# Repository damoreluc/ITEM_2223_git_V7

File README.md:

# Hardware progetto ITEM
## ISIS Bassa Friulana Cervignano del Friuli - ISIS Malignani Udine - Danieli 

Progetto hardware delle schede del sistema di acquisizione dati del _Banco di prova per riduttori meccanici_<br>
Il progetto è realizzato con il cad Eagle.

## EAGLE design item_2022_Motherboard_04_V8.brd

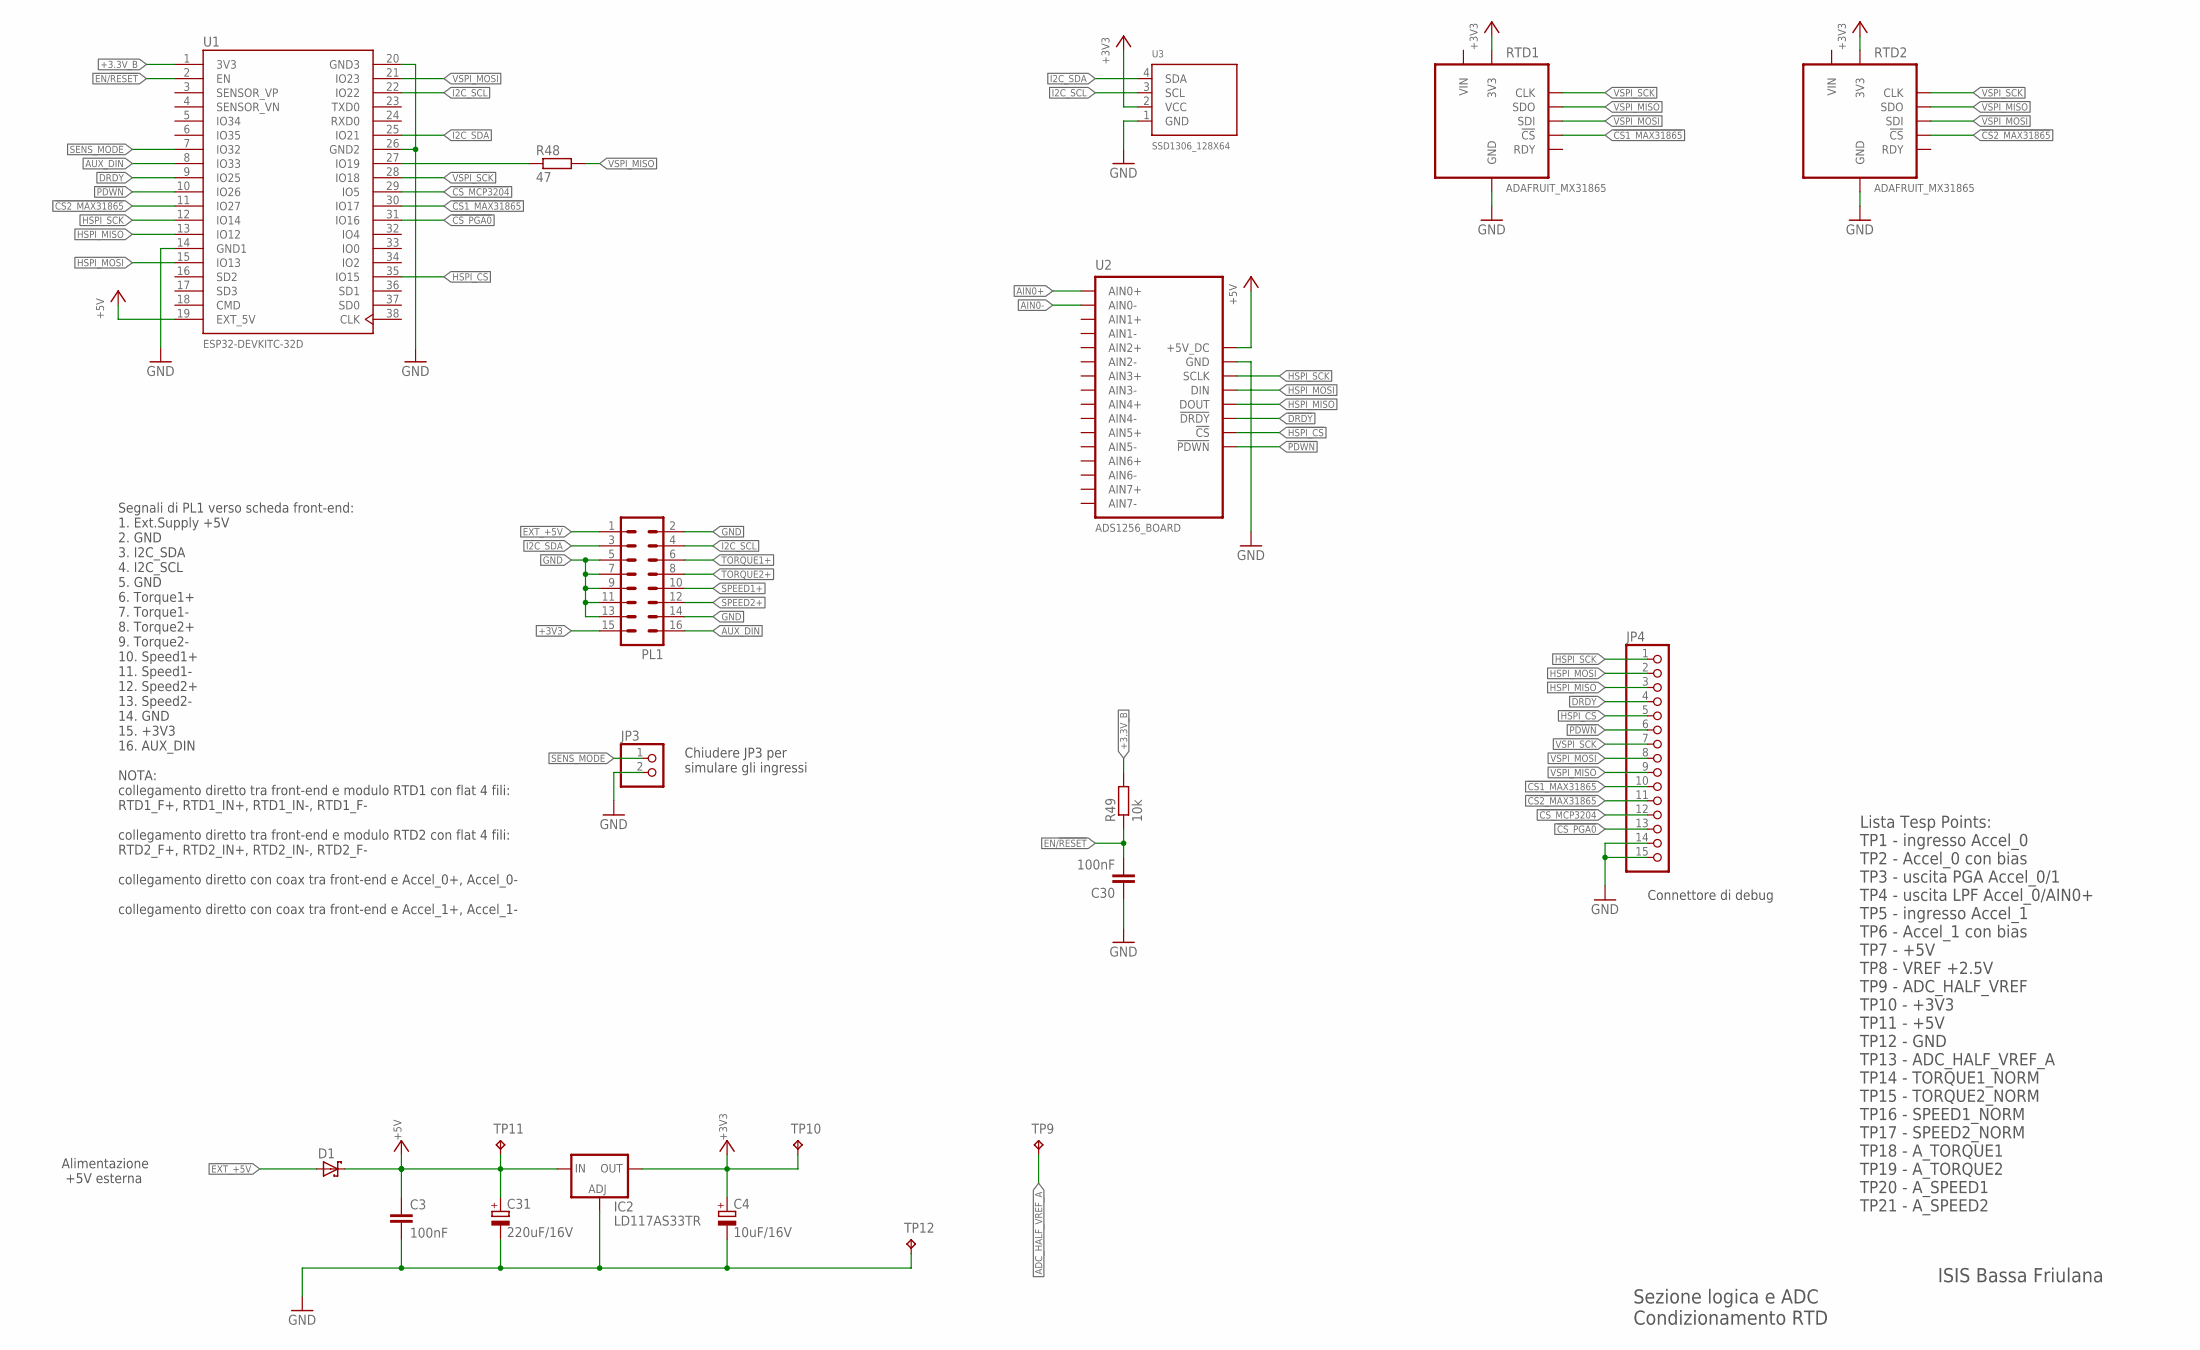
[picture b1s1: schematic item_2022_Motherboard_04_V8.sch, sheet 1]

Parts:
C3: 100nF; C0805K
C4: 10uF/16V; E2,5-6
C30: 100nF; C0805
C31: 220uF/16V; E3,5-10
D1: SCHOTTKY-DIODEDO35-7; DO35-7
IC2: LD117AS33TR; SOT223
JP3: PINHD-1X2; 1X02
JP4: PINHD-1X15; 1X15
PL1: 16H
R48: 47; R0805
R49: 10k; R0805
RTD1, RTD2: ADAFRUIT_MX31865; ADAFRUIT_MAX31865
TP9, TP10, TP11: TPTP16SQ; TP16SQ
TP12: TPTP14R; TP14R
U1: ESP32-DEVKITC-32D; MODULE_ESP32-DEVKITC-32D
U2: ADS1256_BOARD
U3: SSD1306_128X64; 128X64

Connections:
!CS1_MAX31865!: JP4.10, RTD1.P7 (!CS!), U1.30 (IO17)
!CS2_MAX31865!: JP4.11, RTD2.P7 (!CS!), U1.11 (IO27)
!CS_MCP3204!: JP4.12, U1.29 (IO5); also elsewhere on the board
!CS_PGA0!: JP4.13, U1.31 (IO16); also elsewhere on the board
!DRDY!: JP4.4, U1.9 (IO25), U2.!DRDY!
!HSPI_CS!: JP4.5, U1.35 (IO15), U2.!CS!
!PDWN!: JP4.6, U1.10 (IO26), U2.PDWN (!PDWN!)
+3.3V_B: R49.2, U1.1 (3V3)
+3V3: C4.+, IC2.4 (OUT), PL1.15, RTD1.P3 (3V3), RTD2.P3 (3V3), TP10.TP, U3.2 (VCC); also elsewhere on the board
+5V: C3.1, C31.+, D1.C, IC2.3 (IN), TP11.TP, U1.19 (EXT_5V), U2.5V_DC (+5V_DC); also elsewhere on the board
ADC_HALF_VREF_A: TP9.TP; also elsewhere on the board
AIN0+: U2.AIN0+; also elsewhere on the board
AIN0-: U2.AIN0-; also elsewhere on the board
AUX_DIN: PL1.16, U1.8 (IO33)
EN/!RESET!: C30.2, R49.1, U1.2 (EN)
EXT_+5V: D1.A, PL1.1
GND: C3.2, C4.-, C30.1, C31.-, IC2.1 (ADJ), JP3.2, JP4.14, JP4.15, PL1.2, PL1.5, PL1.7, PL1.9, PL1.11, PL1.13, PL1.14, RTD1.P2 (GND), RTD2.P2 (GND), TP12.TP, U1.14 (GND1), U1.20 (GND3), U1.26 (GND2), U2.GND, U3.1 (GND); also elsewhere on the board
HSPI_MISO: JP4.3, U1.13 (IO12), U2.DOUT
HSPI_MOSI: JP4.2, U1.15 (IO13), U2.DIN
HSPI_SCK: JP4.1, U1.12 (IO14), U2.SCLK
I2C_SCL: PL1.4, U1.22 (IO22), U3.3 (SCL)
I2C_SDA: PL1.3, U1.25 (IO21), U3.4 (SDA)
unnamed: R48.1, U1.27 (IO19)
SENS_MODE: JP3.1, U1.7 (IO32)
SPEED1+: PL1.10; also elsewhere on the board
SPEED2+: PL1.12; also elsewhere on the board
TORQUE1+: PL1.6; also elsewhere on the board
TORQUE2+: PL1.8; also elsewhere on the board
VIN: RTD1.P1 (VIN), RTD2.P1 (VIN)
VSPI_MISO: JP4.9, R48.2, RTD1.P5 (SDO), RTD2.P5 (SDO); also elsewhere on the board
VSPI_MOSI: JP4.8, RTD1.P6 (SDI), RTD2.P6 (SDI), U1.21 (IO23); also elsewhere on the board
VSPI_SCK: JP4.7, RTD1.P4 (CLK), RTD2.P4 (CLK), U1.28 (IO18); also elsewhere on the board

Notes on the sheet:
Sezione logica e ADC Condizionamento RTD
ISIS Bassa Friulana
Lista Tesp Points: TP1 - ingresso Accel_0 TP2 - Accel_0 con bias TP3 - uscita PGA Accel_0/1 TP4 - uscita LPF Accel_0/AIN0+ TP5 - ingresso Accel_1 TP6 - Accel_1 con bias TP7 - +5V TP8 - VREF +2.5V TP9 - ADC_HALF_VREF TP10 - +3V3 TP11 - +5V TP12 - GND TP13 - ADC_HALF_VREF_A TP14 - TORQUE1_NORM TP15 -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
Segnali di PL1 verso scheda front-end: 1. Ext.Supply +5V 2. GND 3. I2C_SDA 4. I2C_SCL 5. GND 6. Torque1+ 7. Torque1- 8. Torque2+ 9. Torque2- 10. Speed1+ 11. Speed1- 12. Speed2+ 13. Speed2- 14. GND 15. +3V3 16. AUX_DIN NOTA: collegamento diretto tra front-end e modulo RTD1 con flat 4 fili: RTD1_F+, 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
Alimentazione +5V esterna
Chiudere JP3 per simulare gli ingressi
Connettore di debug

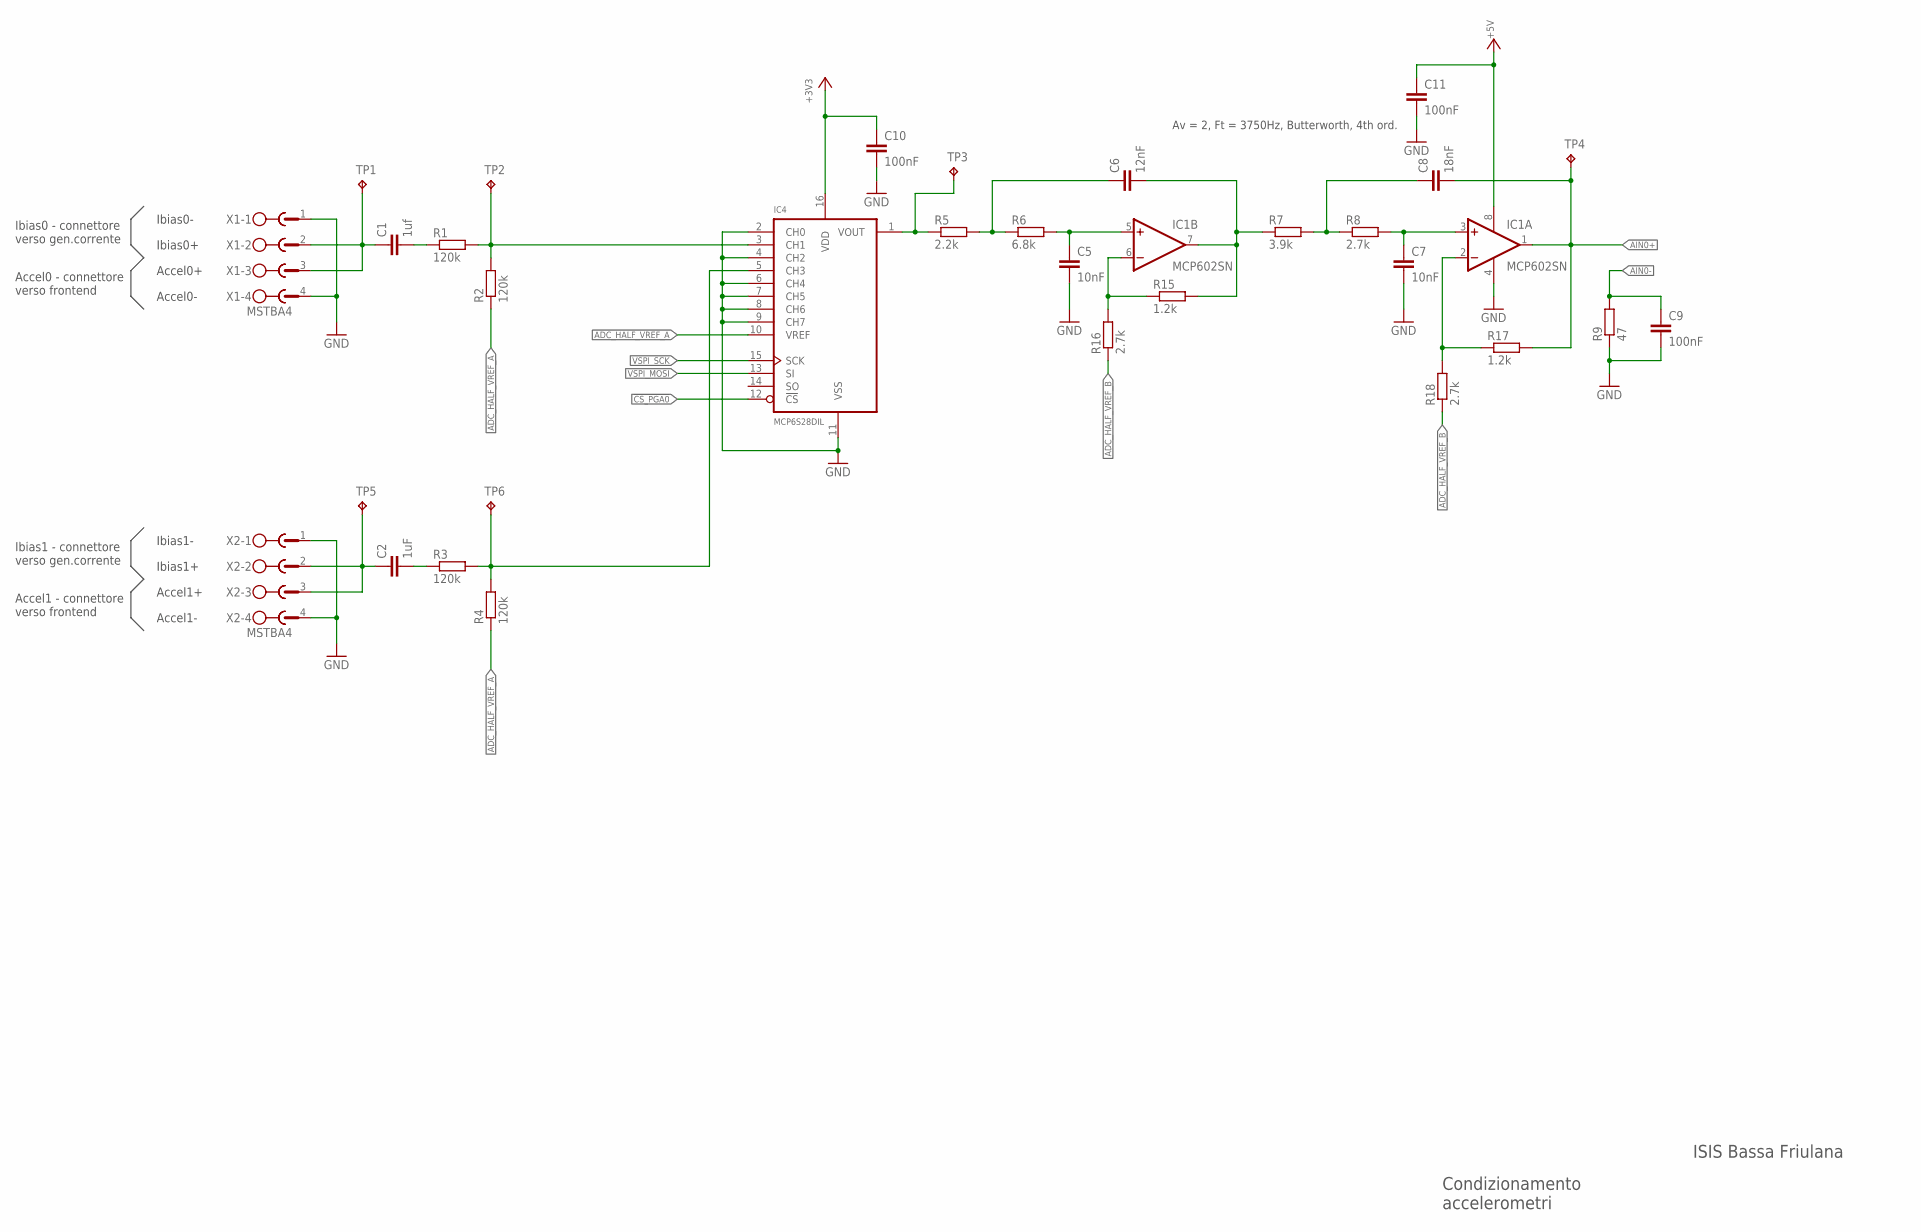
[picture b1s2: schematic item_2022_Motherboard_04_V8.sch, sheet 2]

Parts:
C1: 1uf; C1206
C2: 1uF; C1206
C5, C7: 10nF; C0805K
C6: 12nF; C0805K
C8: 18nF; C0805K
C9, C10, C11: 100nF; C0805K
IC1: MCP602SN; SO08
IC4: MCP6S28DIL; DIL16
R1, R2, R3, R4: 120k; R0805
R5: 2.2k; R0805
R6: 6.8k; R0805
R7: 3.9k; R0805
R8, R16, R18: 2.7k; R0805
R9: 47; R0805
R15, R17: 1.2k; R0805
TP1, TP2, TP3, TP4, TP5, TP6: TPTP14R; TP14R
X1, X2: MSTBA4

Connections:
!CS_PGA0!: IC4.12 (!CS!); also elsewhere on the board
+3V3: C10.1, IC4.16 (VDD); also elsewhere on the board
+5V: C11.1, IC1.8 (V+); also elsewhere on the board
ADC_HALF_VREF_A: IC4.10 (VREF), R2.1, R4.1; also elsewhere on the board
ADC_HALF_VREF_B: R16.1, R18.1; also elsewhere on the board
AIN0+: C8.2, IC1.1 (OUT), R17.2, TP4.TP; also elsewhere on the board
AIN0-: C9.1, R9.2; also elsewhere on the board
GND: C5.2, C7.2, C9.2, C10.2, C11.2, IC1.4 (V-), IC4.2 (CH0), IC4.4 (CH2), IC4.6 (CH4), IC4.7 (CH5), IC4.8 (CH6), IC4.9 (CH7), IC4.11 (VSS), R9.1, X1.1, X1.4, X2.1, X2.4; also elsewhere on the board
unnamed: C1.1, TP1.TP, X1.2, X1.3
unnamed: C2.1, TP5.TP, X2.2, X2.3
unnamed: IC4.3 (CH1), R1.2, R2.2, TP2.TP
unnamed: IC4.1 (VOUT), R5.1, TP3.TP
unnamed: C1.2, R1.1
unnamed: C2.2, R3.1
unnamed: IC1.6 (-IN), R15.1, R16.2
unnamed: C6.1, R5.2, R6.1
unnamed: C5.1, IC1.5 (+IN), R6.2
unnamed: C6.2, IC1.7 (OUT), R7.1, R15.2
unnamed: C8.1, R7.2, R8.1
unnamed: C7.1, IC1.3 (+IN), R8.2
unnamed: IC4.5 (CH3), R3.2, R4.2, TP6.TP
unnamed: IC1.2 (-IN), R17.1, R18.2
VSPI_MOSI: IC4.13 (SI); also elsewhere on the board
VSPI_SCK: IC4.15 (SCK); also elsewhere on the board

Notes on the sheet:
Condizionamento accelerometri
ISIS Bassa Friulana
Av = 2, Ft = 3750Hz, Butterworth, 4th ord.
Accel0 - connettore verso frontend
Accel0+
Accel0-
Ibias0 - connettore verso gen.corrente
Ibias0-
Ibias0+
Accel1 - connettore verso frontend
Accel1+
Accel1-
Ibias1 - connettore verso gen.corrente
Ibias1-
Ibias1+

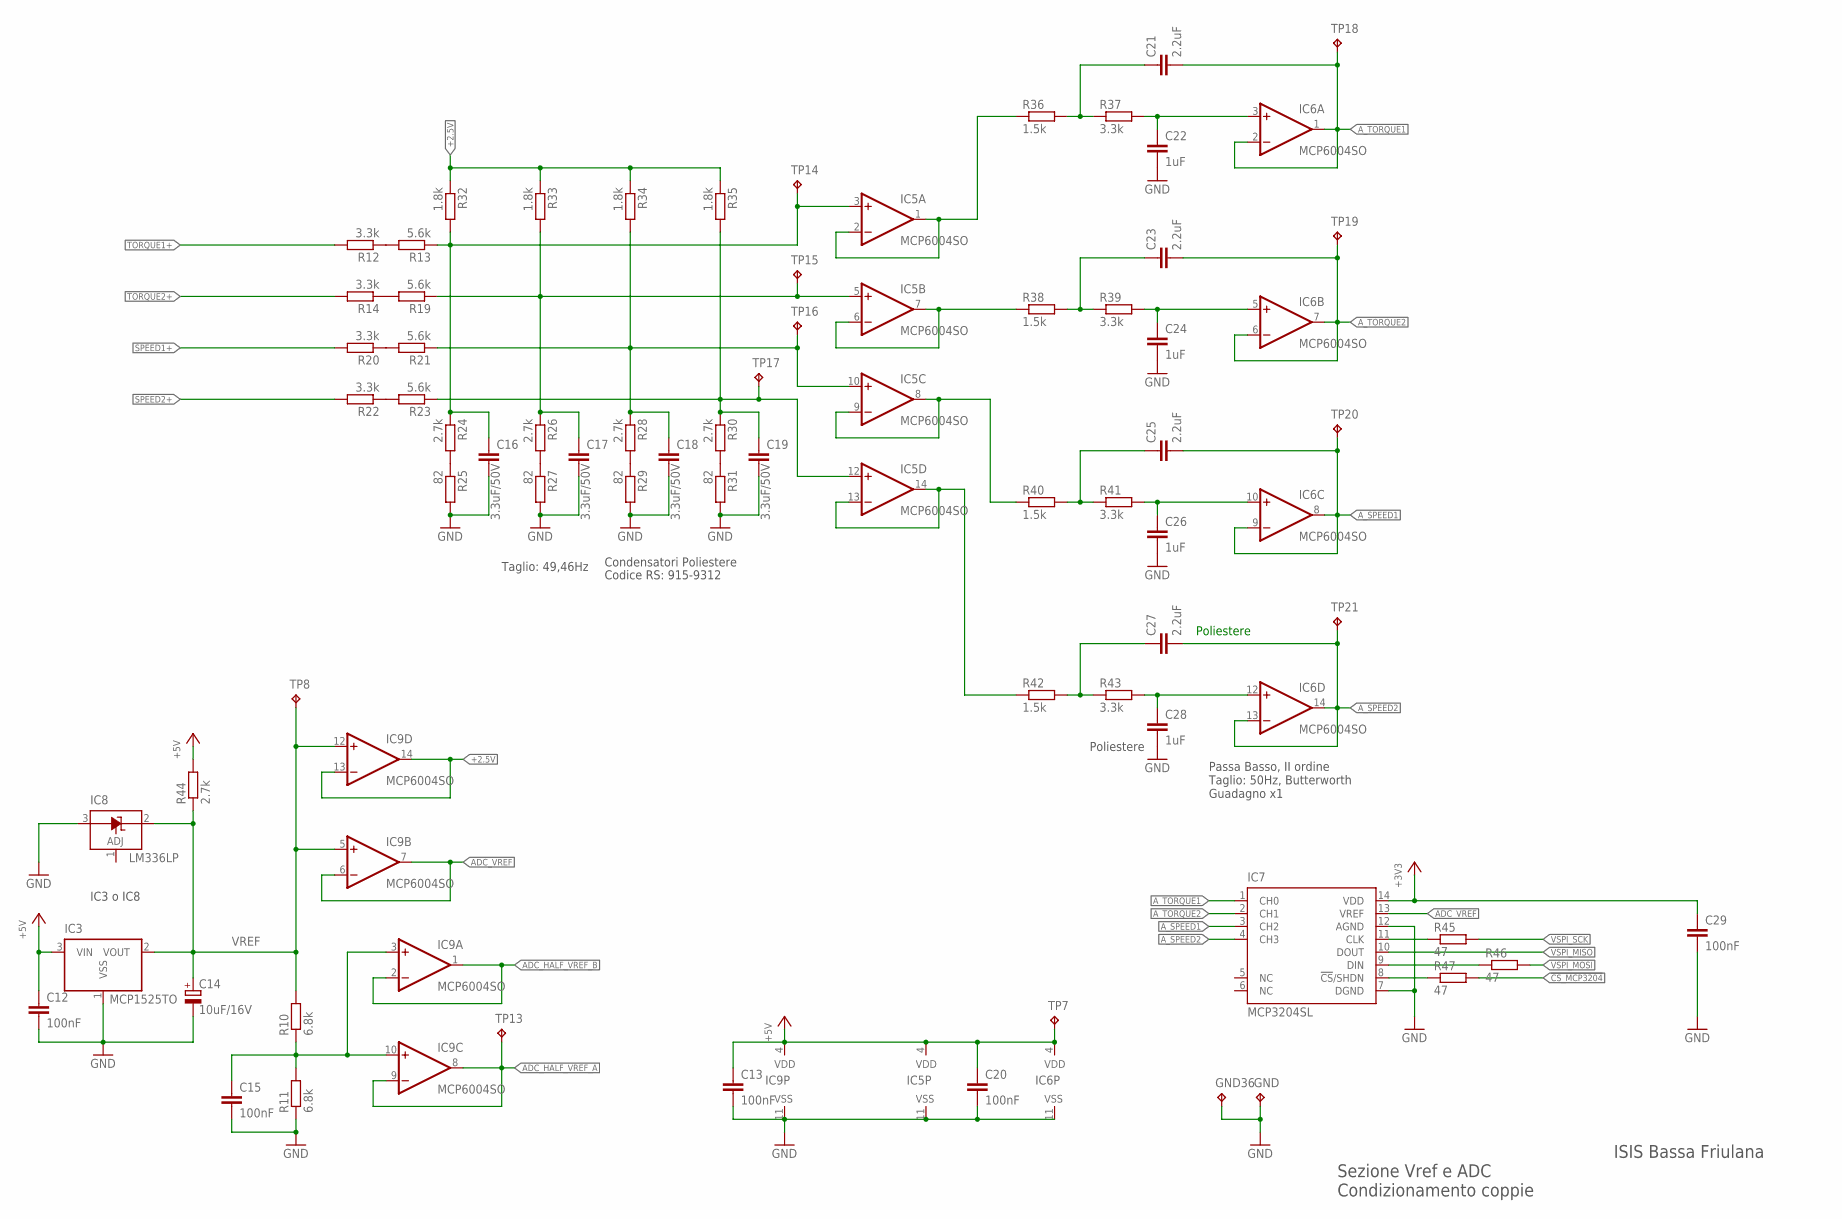
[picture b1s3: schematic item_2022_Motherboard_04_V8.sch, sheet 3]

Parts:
C12, C13, C15, C20, C29: 100nF; C0805
C14: 10uF/16V; E2,5-6
C16, C17, C18, C19: 3.3uF/50V; C0805
C21, C23, C25, C27: 2.2uF; C0805
C22, C24, C26, C28: 1uF; C0805
GND, GND36: TPTP18SQ; TP18SQ
IC3: MCP1525TO; TO92
IC5, IC6, IC9: MCP6004SO; SO14
IC7: MCP3204SL; SO14
IC8: LM336LP; TO92
R10, R11: 6.8k; R0805
R12, R14, R22, R37, R39, R41, R43: 3.3k; R0805
R13, R19, R21, R23: 5.6k; R0805
R20: 3.3k; M0805
R24, R26, R28, R30, R44: 2.7k; R0805
R25, R27, R29, R31: 82; R0805
R32, R33, R34, R35: 1.8k; R0805
R36, R38, R40, R42: 1.5k; R0805
R45, R46, R47: 47; R0805
TP7, TP8, TP13: TPTP16R; TP16R
TP14, TP15, TP16, TP17, TP18, TP19, TP20, TP21: TPTP14R; TP14R

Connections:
!CS_MCP3204!: R47.2; also elsewhere on the board
+2.5V: IC9.13 (-IN), IC9.14 (OUT), R32.1, R33.1, R34.1, R35.1
+3V3: C29.1, IC7.14 (VDD); also elsewhere on the board
+5V: C12.1, C13.1, C20.1, IC3.3 (VIN), IC5.4 (VDD), IC6.4 (VDD), IC9.4 (VDD), R44.2, TP7.TP; also elsewhere on the board
ADC_HALF_VREF_A: IC9.8 (OUT), IC9.9 (-IN), TP13.TP; also elsewhere on the board
ADC_HALF_VREF_B: IC9.1 (OUT), IC9.2 (-IN); also elsewhere on the board
ADC_VREF: IC7.13 (VREF), IC9.6 (-IN), IC9.7 (OUT)
A_SPEED1: C25.2, IC6.8 (OUT), IC6.9 (-IN), IC7.3 (CH2), TP20.TP
A_SPEED2: C27.2, IC6.13 (-IN), IC6.14 (OUT), IC7.4 (CH3), TP21.TP
A_TORQUE1: C21.2, IC6.1 (OUT), IC6.2 (-IN), IC7.1 (CH0), TP18.TP
A_TORQUE2: C23.2, IC6.6 (-IN), IC6.7 (OUT), IC7.2 (CH1), TP19.TP
GND: C12.2, C13.2, C14.-, C15.2, C16.2, C17.2, C18.2, C19.2, C20.2, C22.2, C24.2, C26.2, C28.2, C29.2, GND.TP, GND36.TP, IC3.1 (VSS), IC5.11 (VSS), IC6.11 (VSS), IC7.7 (DGND), IC7.12 (AGND), IC8.3 (A), IC9.11 (VSS), R11.1, R25.2, R27.2, R29.2, R31.2; also elsewhere on the board
unnamed: C15.1, IC9.3 (+IN), IC9.10 (+IN), R10.1, R11.2
unnamed: R12.1, R13.2
unnamed: R14.1, R19.2
unnamed: R20.1, R21.2
unnamed: R22.1, R23.2
unnamed: R24.2, R25.1
unnamed: C16.1, IC5.3 (+IN), R13.1, R24.1, R32.2, TP14.TP
unnamed: R26.2, R27.1
unnamed: R28.2, R29.1
unnamed: R30.2, R31.1
unnamed: C17.1, IC5.5 (+IN), R19.1, R26.1, R33.2, TP15.TP
unnamed: C18.1, IC5.10 (+IN), R21.1, R28.1, R34.2, TP16.TP
unnamed: C19.1, IC5.12 (+IN), R23.1, R30.1, R35.2, TP17.TP
unnamed: IC5.1 (OUT), IC5.2 (-IN), R36.1
unnamed: IC5.6 (-IN), IC5.7 (OUT), R38.1
unnamed: IC5.8 (OUT), IC5.9 (-IN), R40.1
unnamed: IC5.13 (-IN), IC5.14 (OUT), R42.1
unnamed: C21.1, R36.2, R37.1
unnamed: C22.1, IC6.3 (+IN), R37.2
unnamed: C23.1, R38.2, R39.1
unnamed: C24.1, IC6.5 (+IN), R39.2
unnamed: C25.1, R40.2, R41.1
unnamed: C26.1, IC6.10 (+IN), R41.2
unnamed: C27.1, R42.2, R43.1
unnamed: C28.1, IC6.12 (+IN), R43.2
unnamed: IC7.11 (CLK), R45.1
unnamed: IC7.9 (DIN), R46.1
unnamed: IC7.8 (!CS!/SHDN), R47.1
SPEED1+: R20.2; also elsewhere on the board
SPEED2+: R22.2; also elsewhere on the board
TORQUE1+: R12.2; also elsewhere on the board
TORQUE2+: R14.2; also elsewhere on the board
VREF: C14.+, IC3.2 (VOUT), IC8.2 (C), IC9.5 (+IN), IC9.12 (+IN), R10.2, R44.1, TP8.TP
VSPI_MISO: IC7.10 (DOUT); also elsewhere on the board
VSPI_MOSI: R46.2; also elsewhere on the board
VSPI_SCK: R45.2; also elsewhere on the board

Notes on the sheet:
Sezione Vref e ADC Condizionamento coppie
ISIS Bassa Friulana
Condensatori Poliestere
Passa Basso, II ordine Taglio: 50Hz, Butterworth Guadagno x1
Poliestere
Taglio: 49,46Hz
Codice RS: 915-9312
IC3 o IC8

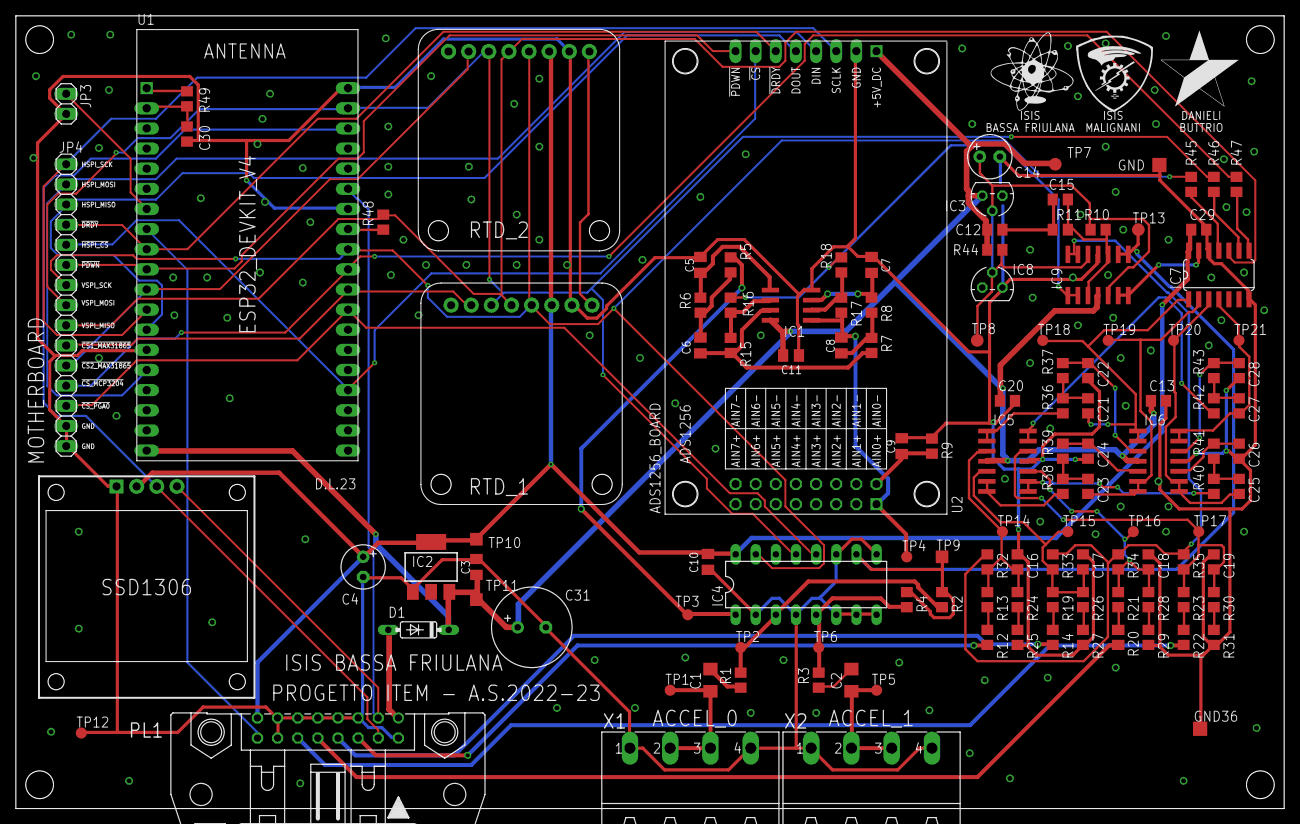
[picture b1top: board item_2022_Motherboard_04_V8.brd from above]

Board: 2 copper layers, 160.0 x 100.0 mm, 126 parts (1 on the bottom side), 82 nets.

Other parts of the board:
U$1: BASSA
U$2: UDINE
U$3: DANIELI

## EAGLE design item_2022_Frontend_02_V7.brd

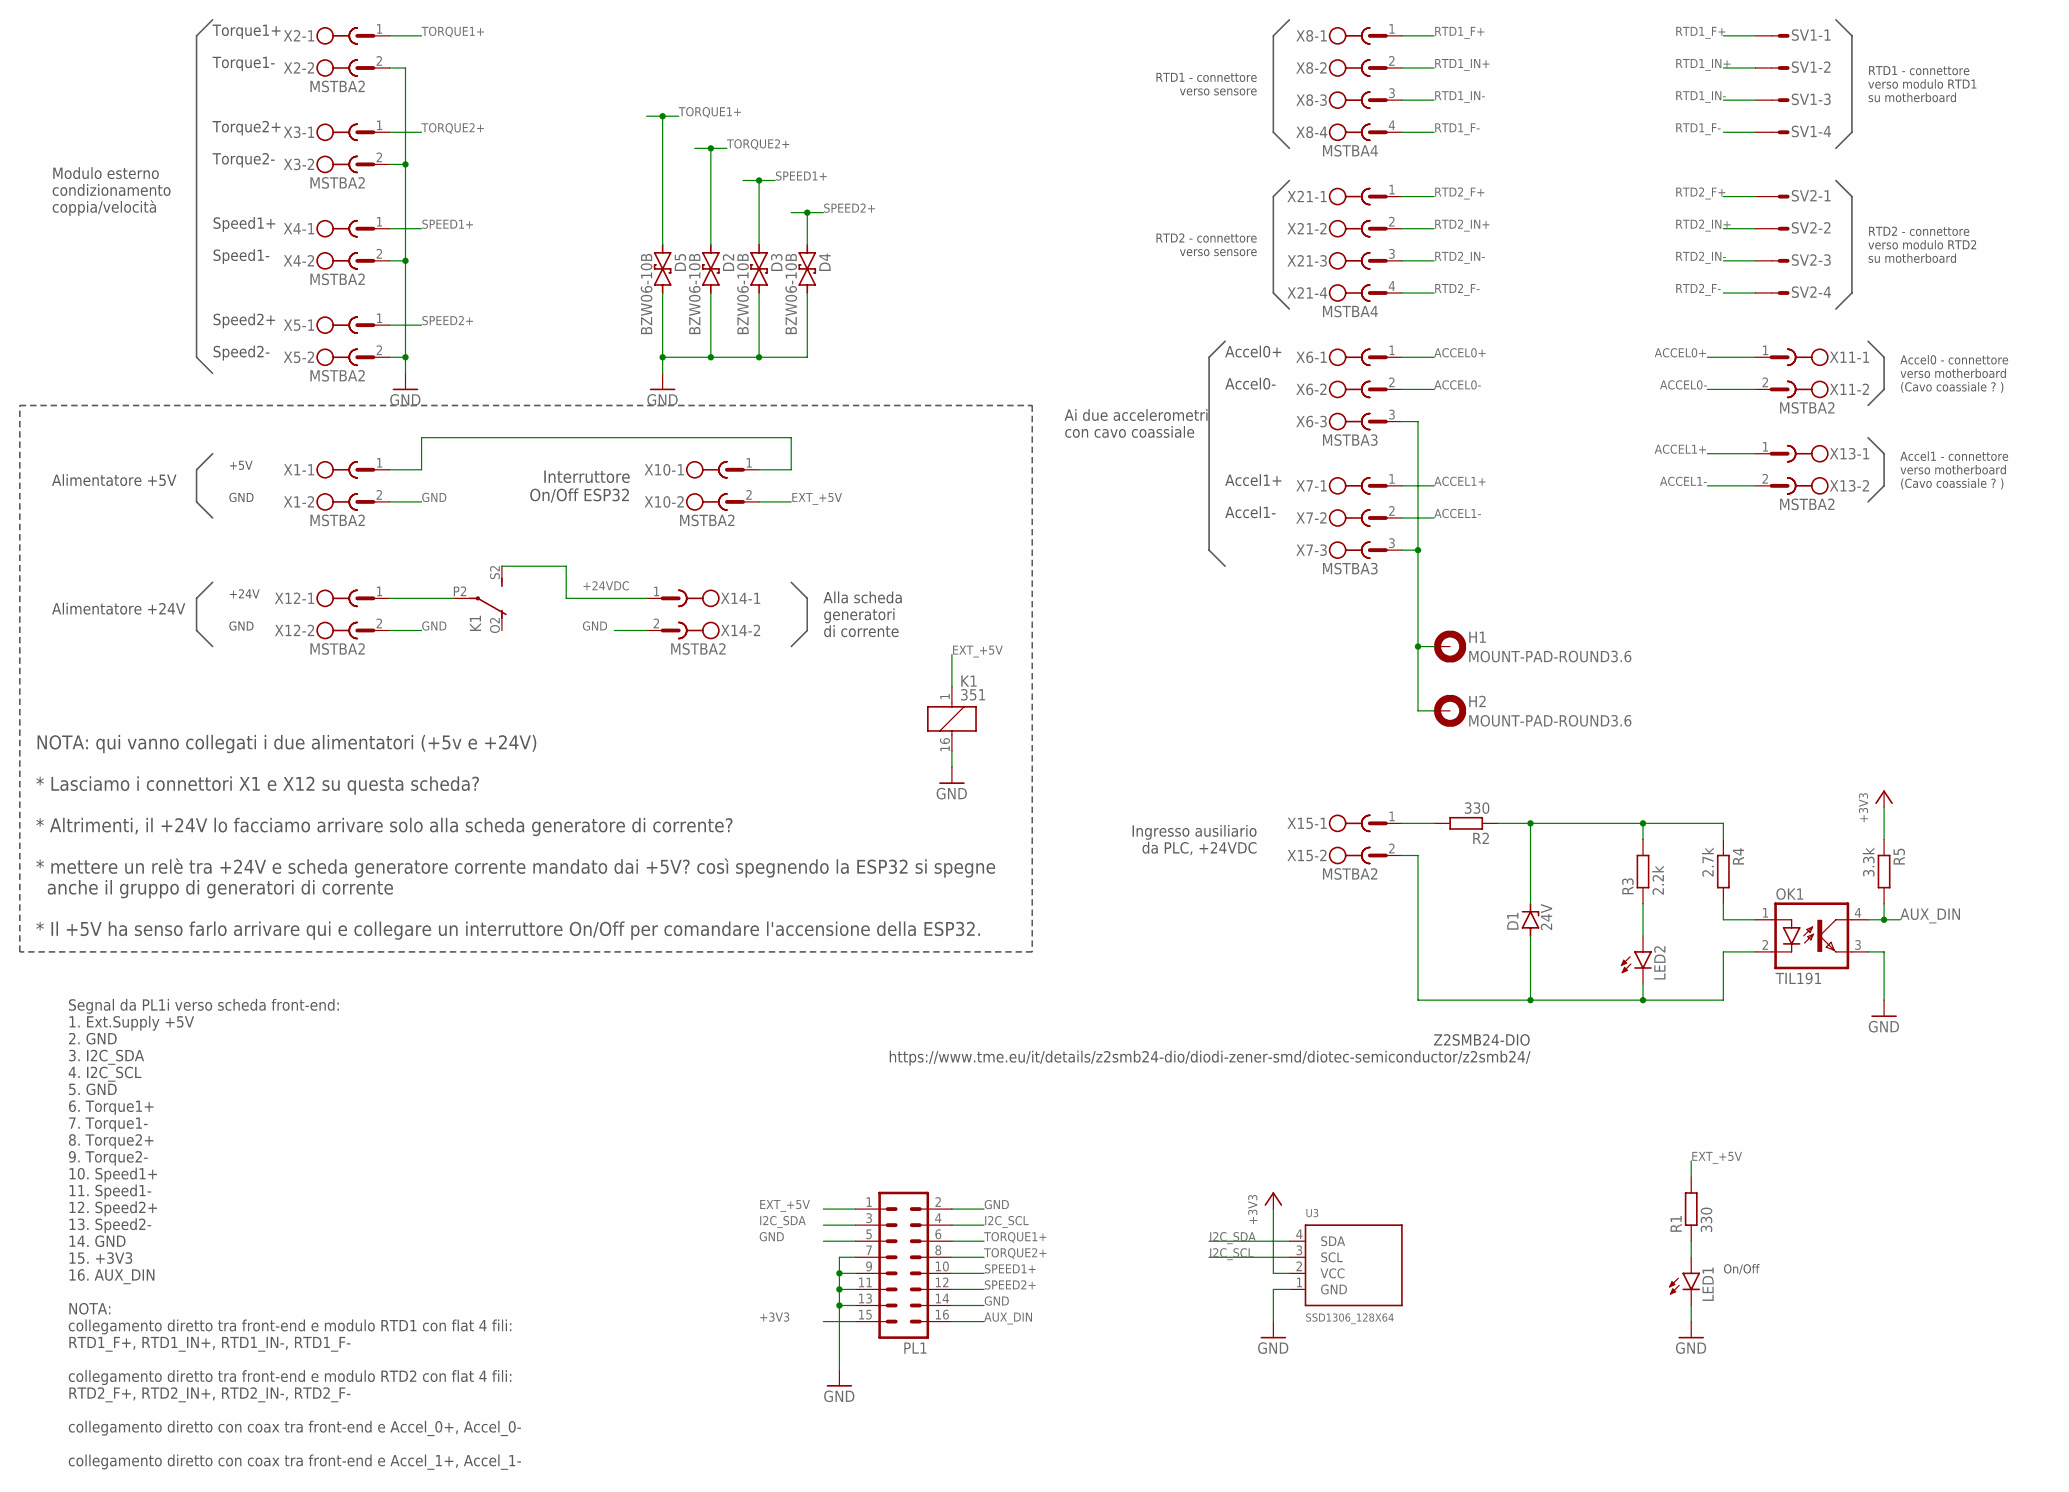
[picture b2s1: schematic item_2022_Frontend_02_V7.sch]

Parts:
D1: 24V; DO35Z10
D2, D3, D4, D5: BZW06-10B; F126Z12
H1, H2: MOUNT-PAD-ROUND3.6; 3,6-PAD
K1: 351
LED1, LED2: LED5MM
OK1: TIL191; DIL04
PL1: 16H
R1, R2: 330; R0805
R3: 2.2k; R0805
R4: 2.7k; R0805
R5: 3.3k; R0805
SV1, SV2: S04P
U3: SSD1306_128X64; 128X64
X1, X2, X3, X4, X5, X10, X11, X12, X13, X14, X15: MSTBA2
X6, X7: MSTBA3
X8, X21: MSTBA4

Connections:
+3V3: PL1.15, R5.1, U3.2 (VCC)
+24VDC: K1.S2 (S), X14.1
ACCEL0+: X6.1, X11.1
ACCEL0-: X6.2, X11.2
ACCEL1+: X7.1, X13.1
ACCEL1-: X7.2, X13.2
AUX_DIN: OK1.4 (COL), PL1.16, R5.2
EXT_+5V: K1.1, PL1.1, R1.2, X10.2
GND: D2.C (2), D3.C (2), D4.C (2), D5.C (2), K1.16 (2), LED1.K (C), OK1.3 (EMIT), PL1.2, PL1.5, PL1.7, PL1.9, PL1.11, PL1.13, PL1.14, U3.1 (GND), X1.2, X2.2, X3.2, X4.2, X5.2, X12.2, X14.2
I2C_SCL: PL1.4, U3.3 (SCL)
I2C_SDA: PL1.3, U3.4 (SDA)
unnamed: R2.2, X15.1
unnamed: X1.1, X10.1
unnamed: LED1.A, R1.1
unnamed: D1.C, R2.1, R3.2, R4.1
unnamed: D1.A, LED2.K (C), OK1.2 (C), X15.2
unnamed: K1.P2, X12.1
unnamed: LED2.A, R3.1
unnamed: OK1.1 (A), R4.2
PE: H1.B3,6, H2.B3,6, X6.3, X7.3
RTD1_F+: SV1.1, X8.1
RTD1_F-: SV1.4, X8.4
RTD1_IN+: SV1.2, X8.2
RTD1_IN-: SV1.3, X8.3
RTD2_F+: SV2.1, X21.1
RTD2_F-: SV2.4, X21.4
RTD2_IN+: SV2.2, X21.2
RTD2_IN-: SV2.3, X21.3
SPEED1+: D3.A (1), PL1.10, X4.1
SPEED2+: D4.A (1), PL1.12, X5.1
TORQUE1+: D5.A (1), PL1.6, X2.1
TORQUE2+: D2.A (1), PL1.8, X3.1

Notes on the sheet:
Segnal da PL1i verso scheda front-end: 1. Ext.Supply +5V 2. GND 3. I2C_SDA 4. I2C_SCL 5. GND 6. Torque1+ 7. Torque1- 8. Torque2+ 9. Torque2- 10. Speed1+ 11. Speed1- 12. Speed2+ 13. Speed2- 14. GND 15. +3V3 16. AUX_DIN NOTA: collegamento diretto tra front-end e modulo RTD1 con flat 4 fili: RTD1_F+, 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
Interruttore On/Off ESP32
Alimentatore +5V
+5V
GND
Torque1+
Torque1-
Torque2+
Torque2-
Speed1+
Speed1-
Speed2+
Speed2-
Accel0+
Accel0-
Accel1+
Accel1-
RTD1 - connettore verso sensore
RTD2 - connettore verso sensore
RTD1 - connettore verso modulo RTD1 su motherboard
RTD2 - connettore verso modulo RTD2 su motherboard
Ai due accelerometri con cavo coassiale
Modulo esterno condizionamento coppia/velocità
Alimentatore +24V
+24V
Accel0 - connettore verso motherboard (Cavo coassiale ? )
Accel1 - connettore verso motherboard (Cavo coassiale ? )
NOTA: qui vanno collegati i due alimentatori (+5v e +24V) * Lasciamo i connettori X1 e X12 su questa scheda? * Altrimenti, il +24V lo facciamo arrivare solo alla scheda generatore di corrente? * mettere un relè tra +24V e scheda generatore corrente mandato dai +5V? così spegnendo la ESP32 si spegne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
On/Off
Alla scheda generatori di corrente
Ingresso ausiliario da PLC, +24VDC
Z2SMB24-DIO https://www.tme.eu/it/details/z2smb24-dio/diodi-zener-smd/diotec-semiconductor/z2smb24/

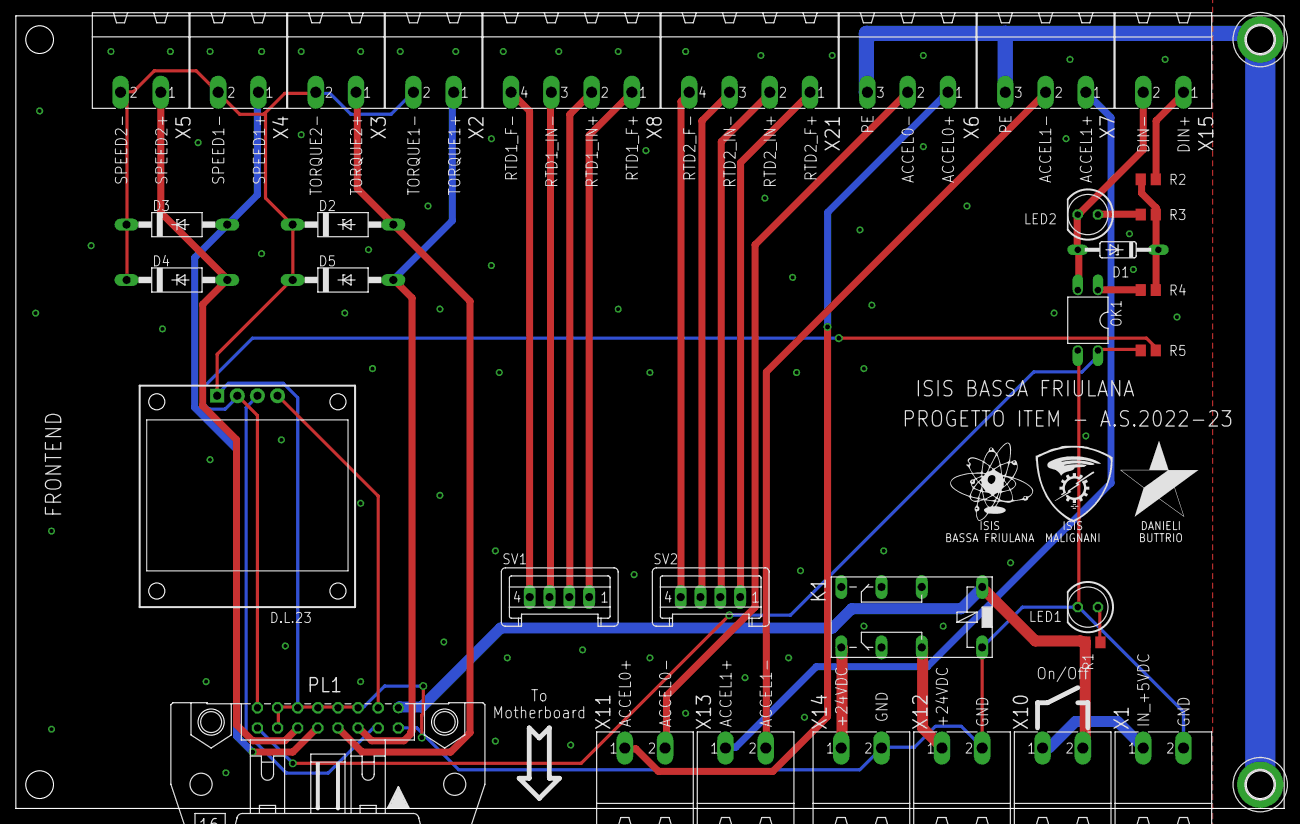
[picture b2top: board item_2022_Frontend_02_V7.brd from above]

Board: 2 copper layers, 160.0 x 100.0 mm, 38 parts (0 on the bottom side), 32 nets.

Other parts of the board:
U$1: BASSA
U$2: UDINE
U$3: DANIELI
